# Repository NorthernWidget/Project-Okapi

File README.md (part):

# Okapi: Data logger with integrated solar charging and modular telemetry

***Okapi data logger (Resnik v0.4.0), with a micro-SD card for local storage and a Particle Boron telemetry module.***

The **Okapi** data logger responds to the need for a robust, flexible, and power-efficient open-source option to record and transmit data from remote locations. It is programmable using the open-source standard Arduino framework via a standard USB-C cable and supports a wide range of sensor input/output options. It connects to dual power supplies to ensure consistent recordings, and interfaces with a range of “Feather”-form-factor boards for telemetry.

## Namesake

The Okapi, a relative of the giraffe, communicates over long distances using [infrasound](https://en.wikipedia.org/wiki/Infrasound). The telemetry capabilities of this data logger inspired this namesake.

## Technical specifications

### Electronic Hardware

* Microcontroller (computer) core
  * ATMega1284p
  * Arduino compatible
  * Programmable using C++
  * 8 MHz
* Real-time clock
  * DS3231M
  * Temperature-compensated crystal for high accuracy (±5 ppm)
* Sensor and general-purpose connections
  * Primary Rail (selectable 3.3V or 5V)
    * I2C (up to 128 sensors permitted; expansion ports provided by Project Heptapod)
    * SPI
    * 2x 16-bit analog
    * Analog voltage reference
    * 12-bit Digital-to-analog conversion
    * 2x General-purpose input/output
    * USART
    * 2x Vbus (selectable 3.3V or 5V)
    * 2x Ground
  * Secondary Rail (selectable 3.3V or 5V)
    * I2C (up to 128 sensors permitted; expansion ports provided by Project Heptapod)
    * 2x 16-bit analog
    * 2x General-purpose input/output
    * USART
    * 2x Vbus (selectable 3.3V or 5V)
    * 2x Ground
* Data storage and return
  * Local storage: micro SD card
  * Telemetry: support for Feather-profile boards, including Particle devices:
    * Mobile phone networks
    * WiFi
    * Bluetooth
    * [In development] Iridium satellite
* Power
  * Dual power supply
  * Primary Power
    * Built-in maximum-power-point-tracking solar-charge-control circuitry
    * Lithium-Ion battery
  * Backup Power
    * Alkaline AA batteries
  * Real-time clock
    * Coin cell
  * Power consumption
    * Primary power, sleeping: 80 μA
    * Backup power, sleeping: 4 μA
    * Active (typical: data logger without sensors): 10 mA
    * Transmitting (mobile networks, typical: Particle Boron):
      * 16 mA background
      * 40 mA burst
  * Power generation
  * Solar, low light: 100 mA
* User interface
  * “Log” button: instantaneous reading (for testing)
  * “Reset” button
  * 2x 3-color indicator LEDs for the logger, a 3-color LED for the B-series module, and eight single LEDs on a PCA9634 LED driver
  * Computer readout via a serial monitor, included in the Arduino software
* Open-source licensing via CC BY-SA 4.0

>> @bschulz1701: Any updates needed? I think that there is also a WDT (correct?)

### Electronic Software and Firmware

* Programmable using the Arduino IDE https://www.arduino.cc/en/main/software
* Custom bootloader and board definition for ATMega1284p available via https://github.com/NorthernWidget/Arduino_Boards
* Custom libraries from Northern Widget and the open-source community
  * Primary data-logger functions
  * Libraries available with each sensor, exposing a standard interface
* Open-source licensing via GNU GPL 3.0

### Pinout and board interfaces

***Okapi data logger (Resnik v0.4.0) with pins, connectors, and interactive items annotated.***

**Pins are colored following this convention:**
* Ground: black
* Power supply: red
* Universal Serial Asynchronous Receiver--Transmitter (USART or UART): blue
* General-purpose I/O pins: gray
* Analog inputs and associated reference voltage: green
* Digital communications buses (SPI and I2C): purple
* Analog adjustable voltage output: salmon

**The power and programming connectors at the "south" end of the board are as follows:**
* USB-C connector (J10), to the logger's USB-serial converter (FT231X)
  * May be programmed using any USB-C cable that is not charging-only (i.e. that can carry data)
  * Can be used with our [clock-setting program](https://github.com/NorthernWidget/SetTime_GUI) to set the time on the real-time clock.
  * Provides power to the data logger while it is connected; this power source is isolated from the batteries and solar panel, and therefore may be plugged in safely at any time.
* Micro-USB connector (USB2), wired to the USB port of the B-series SoM on the M.2 socket, for that module rather than the logger
* Solar panel, up to 16 V open-circuit. A wide range of panels can work with this: as built the charger starts at 7.2 V, and [Solar charger set points](#solar-charger-set-points) gives the resistors for other panels. The charger accepts up to 32 V, but the v0.7.0 board's input capacitor (C10) is rated 16 V; [#44](https://github.com/NorthernWidget/Project-Okapi/issues/44) brings the full range in v0.8.0.
* Li-Ion battery, 2.60--4.475 V. This works with standard 18650 Li-ion batteries. It can work well with just a single battery, but if more storage is required, multiple 18650 batteries may be connected in parallel; we have a circuit-board design to do this: https://github.com/NorthernWidget/LiIon-18650-Parallel. ***CAUTION***: most commercially available multiple-18650-battery holders connect them in series; this voltage is ***TOO HIGH*** for the data logger.
* Primary batteries. This is ideally a pack of 3 primary (i.e., not reusable) Alkaline (or better) AA batteries with a long shelf life. The Okapi data logger will switch to these if its rechargeable power supply shuts down. The internal electronics reduce the quiescent power consumption while under backup power (see the above list of [electronic hardware technical specifications](#electronic-hardware)) and inform the logger about which power supply is being used, allowing it to, for example, reduce or temporarily terminate data transmission.

>> @bschulz1701: Solar panel supply current / size?

**"RST" and "LOG" buttons:**
* Reset ("RST"): stop the program that is currently executing on the main logger and return it to its boot sequence.
* Log Now ("LOG"): take a reading immediately. This is useful for diagnoses and testing.

>> General note: we may want to have an LED flash whenever the logger takes a reading -- even for 1/10 of a second. With an option to disable this, of course. But it is often better to know while in the field that a system is working

**Other notes, clockwise from the top:**
* The socket holds a [Feather-form-factor board](https://learn.adafruit.com/adafruit-feather/feather-specification).
  * This standard, designed by [Adafruit](https://www.adafruit.com/), has been widely adopted, including by the IoT/telemetry module designer [Particle](https://www.particle.io/).
  * We often use a [Particle Boron mobile-phone telemetry unit](https://docs.particle.io/boron/).
* Mounting holes for [\#4 screws](https://www.mcmaster.com/91772A106/)
* CR1220 battery; can power the real-time clock for up to 7 years
* ISP header (also called an ICSP header): This 3x2 header is used with an in-system programmer (in-circuit system programmer) to upload the [bootloader](#installing-the-bootloader) to the data logger.
* A micro-SD card holds a copy of all data, whether or not any telemetry is used

>> @bschulz1701: check my clock 7-year figure

***Okapi data logger (Resnik v0.4.0) with key microchips, LEDs, and switches marked.*** *MCU: Microcontroller. RTC: Real-time clock. LED: Light-emitting diode. Bus: a subsystem for connections and data transfer.*

The Okapi data logger contains two buses (see above), each of which has an independent voltage. The primary bus is on the left and the secondary bus is on the right. These can be selected as 3.3V (switches slid towards the inside of the board) or 5V (switches towards the outside of the board).

>> @bschulz1701: How much power can each bus source/sink?

Two LEDs, status and auxiliary, flash messages to the user to provide information on proper operations vs. a variety of possible errors. These are useful for field diagnoses, and are further described in [the field guide section, below](#field-operators-guide).

>> Design note: move STAT label to left of LED so it can be better seen

The Li-ion override button, which can be pressed with the tip of a pen or other small object, ...

>> @bschulz1701: This somehow overrides the Li-Ion battery electronics to allow something to happen... but I am not remembering what!

## On-board Devices

### I2C

| **Device** | **Address** | **Reprogrammable address** | **Function** |
|---|---|---|---|
| MLX90393 | 0x0C | N | Magnetometer |
| PAC1934 | 0x10 | N (R51) | Power monitor on the V_LI, V_PRIME, V_BETA and V_SOLAR_IN rails |
| BMA456 | 0x18 | N | Accelerometer |
| [MCP23018](https://github.com/NorthernWidget-Skunkworks/MCP23018) | 0x20 | N | I/O Expander |
| VEML6030 | 0x48 | N | Ambient light |
| [ADS1115](https://github.com/adafruit/Adafruit_ADS1X15) | 0x49 | N | ADC (sensor port), on the 5 V bus segment |
| MB85RC512T | 0x50 | N | FRAM |
| PCA9634 | 0x52 (also 0x03 and 0x70) | N | LED driver |
| MCP4726A2 | 0x62 | N | DAC, on the 5 V bus segment |
| [DS3231M](https://github.com/NorthernWidget/DS3231_Logger) | 0x68 | N | Real-time clock |
| [BME280](https://github.com/NorthernWidget/BME_Library) | 0x77 | N | On-board barometric pressure, temperature, and relative humidity |

### SPI

* SD Card

### UART (USART)

* FTDI USB-Serial converter
* Feather form-factor telemetry board; typically [Particle Boron](https://docs.particle.io/boron/)

## Assembly

Assembling this data logger is possible by hand with sufficient skill and the following tools:
* Temperature-controlled soldering iron
* Hot-air rework station
* Equipment for stenciling with solder paste
* ESD-safe tweezers and workstation
* Solder wick

Mechanized assembly by a professional circuit-board assembly house, which is available in many parts of the world, may be preferred due to the complexity of this data logger board.

**Do not build v0.7.0.** It is the 2024 design converted to KiCad, and the 2024 design's solar charger has no current-sense resistor: the LT3652's SENSE and BAT pins share one net, so it would charge the LiPo at its switch's current limit and never end the charge ([#32](https://github.com/NorthernWidget/Project-Okapi/issues/32)). v0.8.0 adds the resistor. The v0.7.0 files are the reference for that work.

The files for an assembly house are in `Production/`: the Gerbers, drill files and pick-and-place in `Okapi_0v7_2026-11-13.zip`, and the parts list in `Okapi_BoM_0v7_2026-11-13.csv`. `Production/make_production.sh` builds them from the KiCad design in `Hardware/KiCAD-10import/`. That project reads its symbols, footprints and title block from the Northern Widget KiCad library, [NW-Cold-Silicon](https://github.com/NorthernWidget/NW-Cold-Silicon), cloned into a folder beside this repository; the schematic and board carry their own copies of every symbol and footprint, so they open without it. The KiCad board is the 2024 Eagle board (`Hardware/Okapi.brd`) converted, and its copper, drills and placement match the 2024 fabrication files in `Hardware/Okapi_2024-11-02/` except where a recorded change differs (JP8 and R62 removed, smaller lands under R1, R5, R7, R8, C1 and C22, dual lands for R22, R48 and R69–R71, slots for the micro-USB shell, and the USB-C shell's slots and its link to ground).

>> THOUGHT: I have basic instructions for assembly on the [Project Walrus](https://github.com/NorthernWidget-Skunkworks/Project-TPDH-Walrus) README; I will not reproduce these here just yet, as we might want to set up a separate assembly guide, mostly with good links to existing resources, since our writing something of this nature would be to reinvent the wheel.

## Programming

### Downloading and installing the Arduino IDE

Go to https://www.arduino.cc/en/main/software. Choose the proper IDE version for your computer. For Windows, we suggest the non-app version to have more control over Arduino; this might change in the future. You will have to add custom libraries, so the web version will not work (at least, as of the time of writing). Download and install the Arduino IDE. Open it to begin the next steps.

### Installing the bootloader

Before a data logger can receive programs via the convenient USB port, it must have a *bootloader* that tells it to expect to receive new programs that way.  You can read more about bootloaders in general here: https://www.arduino.cc/en/Hacking/Bootloader.

Because you can't upload the bootloader via USB, you use the 2x3-pin 6-pin ICSP (also called ISP) header with a special device called an "in-circuit system programmer" (or just "in-system programmer; yup, that's what the acronym stands for).

Many devices exist to upload a bootloader including:
* The official [AVR ISP mkII](http://ww1.microchip.com/downloads/en/DeviceDoc/Atmel-42093-AVR-ISP-mkII_UserGuide.pdf) (no longer produced but available used)
* Using an [Arduino as an ISP](https://www.arduino.cc/en/tutorial/arduinoISP)
* The versatile [Olimex AVR-ISP-MK2](https://www.olimex.com/Products/AVR/Programmers/AVR-ISP-MK2/open-source-hardware)
* The [Adafruit USBtinyISP](https://www.adafruit.com/product/46)

To upload the bootloader, do the following:

1. Open the Arduino IDE. If you have not yet installed the Northern Widget board definitions, find and install them here (instructions provided): https://github.com/NorthernWidget/Arduino_Boards
2. Select the desired board -- most likely ***ATMega1284p 8MHz*** under *Northern Widget Boards*.
3. Plug the data logger into your computer via a USB-C cable to provide power.
4. Plug your ISP of choice into your computer (via a USB cable) and onto the 6-pin header. There are two ways to place it on; the header is aligned such that the ribbon cable should be facing away from the board while programming. If this fails without being able to upload, try flipping the header around.
5. Go to Tools --> Programmer and select the appropriate programmer based on what you are using.
6. Go to Tools --> Burn bootloader. Typically, within a few seconds, you learn whether you succeeded or failed. Hopefully it worked!

***Important note for Linux users:*** You must supply permissions to the Arduino IDE for it to be able to use the ICSP, or you will have to run it using `sudo`. The former option is better; the latter is easier in the moment.

***Note: Be sure to download and/or update drivers for your ISP.***

### Installing the requisite software libraries

>> @awickert: Add a full list of the requisite software to install; finish the firmware aggregator and use those directions (or the Arduino ones) to help users install that + sdfat. Include screenshots and host those directions at https://github.com/NorthernWidget-Skunkworks/Firmware-Aggregator.

### How to write a program

The below program is an example that you can copy and paste directly into the Arduino IDE in order to upload to your data logger. We'll walk you through what each piece of the code is and does.

#### Full program
```c++
/*
 * Okapi example: connected with a Walrus pressure--temperature sensor, often
 * used for water-level measurements, via the Longbow I2C/RS-485 translator.
 * Written by Bobby Schulz with a few comments added by Andy Wickert.
 */

#include "Okapi.h"
#include <TP_Downhole_Longbow.h>

TP_Downhole_Longbow Walrus; // Instantiate Walrus sensor; relict library name
Okapi Logger; // Instantiate data logger object

String Header = ""; // Information header; starts as an empty string
uint8_t I2CVals[1] = {0x22}; // I2C addresses of sensors

unsigned long UpdateRate = 60; // Number of seconds between readings

void setup() {
  Header = Header + Walrus.GetHeader();
  Logger.begin(I2CVals, sizeof(I2CVals), Header); // Pass header info to logger
  Init();
}

void loop() {
  Logger.run(Update, UpdateRate);
}

String Update()
{
  Init();
  delay(1500);
  return Walrus.GetString();
}

void Init()
{
  Walrus.begin(13, 0x22); // Instantiate Walrus (at address = 13)
                          // and Longbow Widget (at address = 0x22)
}
```

#### "Include" statements

```c++
#include "Okapi.h"
#include <TP_Downhole_Longbow.h>
```

These bring in the two code libraries involved, the former for the data logger and the latter for the sensors. This allows the user to access the classes and functions within these two libraries, as we will show in more detail below.

#### Instantiate a sensor object

```c++
TP_Downhole_Longbow Walrus; // Instantiate Walrus sensor; relict library name
Okapi Logger; // Instantiate data logger object
```

"Instantiating an object" means that we create our own specific versions of the a class of items. This can be thought of as: `Breakfast myBreakfast`. Breakfast is the general concept, but I create "myBreakfast", which I can then modify. In this same way, "Logger" is what we call our Okapi data logger, and "Walrus" is what we call our "TP_Downhole_Longbow" sensor; this name is a holdover from an earlier design that is the ancestor of the Walrus. We can then access functions and variables within these two instantiated objects.

#### Declare the header string

```c++
String Header = ""; // Information header; starts as an empty string
```

We start with an empty header, but will soon add information to it.

#### Create a list of the I2C addresses of the sensors

```c++
uint8_t I2CVals[1] = {0x22}; // I2C addresses of sensors
```

This is the trickiest step. You need to know what the I2C address of your sensor is. You can skip this, but then the logger will not run a check to see if the sensor is properly connected.

>> Let's make sure that we record this one each page, or find a way to replace this.

#### Declare the amount of time between logging events

```c++
unsigned long UpdateRate = 60; // Number of seconds between readings
```

This is the number of seconds between logging events. If it takes 2 seconds to record data, make sure that you give the logger at least 3 seconds between events. The maximum logging time is set by the watchdog timer, which [FINISH HERE]

>> @BSCHULZ1701: Is there an external WDT on Okapi?

#### `setup()` step: runs once at the start

```c++
void setup() {
  Header = Header + Walrus.GetHeader();
  Logger.begin(I2CVals, sizeof(I2CVals), Header); //Pass header info to logger
  Init();
}
```

`setup()` is a special function that runs just once when the logger boots up. In this case, it first adds the Walrus' header to the header string. `GetHeader()` is a standard function that lies within each of our sensor libraries and returns this header information as a `String`. We then pass the header and the I2C values to the Okapi library's `begin()` function. This sets up the header and prepares the data loger to record data. Finally, this function calls `Init()`, which we skip ahead to describe immediately below.

>> (awickert): I still don't understand why we have to pass `sizeof()` and can't just compute that within the function.

#### `Init()` function: skipping ahead to understand `setup()`

```c++
void Init()
{
  Walrus.begin(13, 0x22); // Instantiate Walrus (at address = 13)
                          // and Longbow Widget (at address = 0x22)
}
```

The `Init()` function calls the `begin()` function, standard within each Northern Widget sensor library, to instantiate the connection ports (e.g., I2C, RS-485) used to communicate between the sensor and the logger. In this case, there is only one sensor, but two ports are needed: An RS-485 signal goes from the Walrus to the Longbow Widget, which then converts the signal into an I2C signal with its own address. The reason for this is that an I2C signal can travel only ~3 m, but an RS-485 signal can travel ~100 m.

#### `loop()` step: keeps running until stopped

```c++
void loop() {
  Logger.run(Update, UpdateRate);
}
```

The loop calls the main function of the Okapi library, `run()`, repeatedly. This puts the logger into a low-power sleep mode and wakes it up only when interrupted by the clock or the "LOG" button. `Update` refers to the function described immediately below. `UpdateRate` is our logging interval defined above.

#### `Update()` function: Gives data for the logger to record

```c++
String Update()
{
  Init();
  delay(1500);
  return Walrus.GetString();
}
```

The `Update()` function first calls the `Init()` function to be sure that the sensor is ready to log. It then in this case delays 1500 milliseconds; this is an ad-hoc solution to the question of how long it takes the pressure transducer to settle after being started up, and is a safe large amount of time. This function then can `return` a string of all of the Walrus' readings (one pressure and two temperature measurements) separated by commas. This is then concatenated to a list of logger-internal measurements -- date/time; on-board temperature, pressure, and relative humidity; and onboard voltages for battery and solar-panel status -- and recorded to the SD card. If telemetry were present, these data could also be sent to a remote location.

### Reference

A full index of the public variables and functions within the Okapi data logger library is available at https://github.com/NorthernWidget/Okapi_Library.

>> Send user to library page

>> Thoughts: We should make all comments compatible with doxygen (following) what I did with the ALog library. It also looks like TravisCI has support for Arduino(!) This means that we could also automate construction of the documentation for these libraries.

### Integration with Particle Boron

>> @bschulz1701?

#### The 66-minute timer

The telemetry module (a Boron on the FeatherWing socket, or a B-SoM on the M.2 socket) is not powered all the time. Its battery input comes through a load switch (U10) that a TPL5111 timer (U8) controls, and the timer runs on its own clock with an interval set by R20: 130 kΩ gives 66 minutes (3943 s by the TPL5111 datasheet's Equation 1; 3854 to 4033 s with a 1 % resistor). The 2024 Eagle files also carry JP8, which selects R62 (330 kΩ) instead. That value is above the part's 170 kΩ maximum and does nothing, and the KiCad board removes both (#34).

Three things happen on that interval:

1. **It powers the module every 66 minutes whether or not the logger asks.** This is the purpose of the timer: a cellular module receives only while it is powered and attached, so the hourly wake is the window in which a command, a request to resend, or a firmware update for the module can arrive from outside, and the slowest the module can ever be heard from is once an interval, even if the ATmega is asleep past its schedule or hung. For that to work the module must connect on every wake, not only when it has rows to send, and then say it is done.
2. **It bounds every session.** From the moment the module is powered, by the timer or by the logger, it has at most one interval before the timer cuts its power for 50 ms and starts over. A module that hangs is power-cycled once an hour, and this is the only reset path to the module on the board.
3. **It is the counter the logger restarts.** Pulling PARTICLE_EN low for 20 to 30 ms (expander port B pin 7, through Q3 onto the timer's DELAY/M_DRV pin) powers the module at once and restarts the interval. Hold it low and the module stays on past the interval, so pulse it. A request while the module is already on is ignored.

The module ends its own session by pulsing WD_DONE (the FeatherWing's A3, the B-SoM's ADC3): the timer drops the switch and the module draws nothing until the next interval or the next request. The 2019 Boron sketch does this from a 90-second watchdog that it refreshes on every line received from the logger, so the module stays up while rows arrive and shuts itself off 90 seconds after the last one.

As of 2026-11-05 the logger firmware does not drive PARTICLE_EN (Okapi_Library's backhaul writes the pin high, which on the open-drain expander releases it, and never configures it as an output), so on the boards in the field the timer alone powers the module and the backhaul succeeds only when it lands inside a module's on-window. The intended cycle, pulse PARTICLE_EN when there are rows to send and let the module pulse DONE when they are sent, is the firmware fix on the list.

## Wiring

>> Example needed

## Power supply

* **Lithium-ion 18650 rechargeable batteries**; this board can hold two in parallel: https://github.com/NorthernWidget/LiIon-18650-Parallel
* **Solar panel**. A wide range is acceptable, but we like [Voltaic Systems' 6-watt panel](https://voltaicsystems.com/6-watt-panel/). If you do not want to snip off the barrel jack, [this extension plug from Adafruit should work](https://www.adafruit.com/product/2788) (though we have not tested it... and you'll also have to cut *it* in half).
* **Primary alkaline batteries**; we typically use three high-quality (e.g., Duracell) AAs. These are the backup power supply, and we place them in a [3xAA holder (in series for the proper voltage) with a switch](https://www.jameco.com/z/SBH-331-AS-R-3x-AA-Battery-Holder-with-Cover-and-Switch_216144.html).

>> @bschulz1701: new smarter 18650 holder?

### Solar charger set points

Two resistor pairs set how the LT3652 charger (U4) uses your panel. Both sit on lands that take an 0402 or an 0603 part, so you can change them by hand to suit the panel you deploy:

* **MPPT, R22 over R69.** The charger holds the panel at 2.7 V × (1 + R22 / R69), close to the panel's maximum-power voltage, and draws less current rather than let the panel sag below it.
* **Start, R71 over R70.** The charger starts once the panel rises above 1.2 V × (1 + R71 / R70). Keep this below the panel's open-circuit voltage. The charger also needs the panel about 3.3 V above the cell to start (7.5 V on a full cell).

| Panel | Examples | R22 / R69 | MPPT | R71 / R70 | Start | Board |
|---|---|---|---|---|---|---|
| 6 V, 12-cell (as built) | Voltaic P126 (2 W); older 6 V panels such as Voltaic's 6 W P106C | 143 kΩ / 100 kΩ | 6.56 V | 1 MΩ / 200 kΩ | 7.2 V | v0.7.0 |
| 5–6 V, 10-cell ETFE | Voltaic P105, P110, P120, P124 | 143 kΩ / 120 kΩ | 5.92 V | 1 MΩ / 205 kΩ | 7.05 V | v0.7.0 |
| 12 V, 36-cell | Campbell SP10 and SP20, Renogy RNG-10D-SS, Ameresco 10M and 20J, Voltaic P108 and P152 | 1 MΩ / 200 kΩ | 16.2 V | 1 MΩ / 100 kΩ | 13.2 V | v0.8.0 |

As built, a 10-cell panel cannot always start the charger: its open-circuit voltage (6.6–7.3 V at 25 °C) sits at or below the 7.2 V start threshold, and lower still on a warm day. Change R70 to 205 kΩ, and R69 to 120 kΩ for the lower maximum-power voltage. A 12 V panel reaches 27 V open-circuit at −40 °C, beyond the 16 V input capacitor on v0.7.0, so 12 V panels wait for v0.8.0 ([#44](https://github.com/NorthernWidget/Project-Okapi/issues/44), [#46](https://github.com/NorthernWidget/Project-Okapi/issues/46)). Panel figures are from the makers' datasheets; the study behind this table is in NW-Status (`studies/okapi-hardware-audit/sources/2026-11-09-solar-panels-agent-report.md`).

### Regulator feedback dividers

The two adjustable regulators set their outputs with resistor dividers that follow their datasheets: the TLV61220 (U1, the 5 V core boost) with R4 1.62 MΩ over R5 180 kΩ, the datasheet's own example value for the lower resistor, and the TPS62822 (U2, the 3.3 V aux buck) with R6 820 kΩ over R7 180 kΩ and C6 68 pF as its feed-forward capacitor, which is the datasheet's 12 ms / R2 exactly.

The TPS62822's divider sits above the datasheet's center value (R2 of 100 kΩ, at most 120 kΩ, for 5 µA in the divider). That is a trade the datasheet names: a lower divider buys noise immunity at the FB node and costs light-load efficiency. Here the divider draws 3.3 µA instead of 6 µA, about 9 µW less from a rail that spends its life at light load and is switched off in sleep, and the node's sensitivity to pin bias and leakage is about twice the datasheet's, which on a regulator with a 1 % reference feeding sensors through their own switches is below anything measurable. Decided 2026-11-05 to keep the values as built (Project-Okapi #22).

### Sensor port current limits

Each sensor bus (PRIME and SEC) is fed through a pair of MIC2544 high-side switches, one from the 5 V rail and one from the 3.3 V rail. A slide switch on each bus (S1 for SEC, S2 for PRIME) picks 5 V or 3.3 V, and the firmware turns the bus on or off. Logic gates make the two choices exclusive: an AND gate passes the bus enable to the 5 V switch only when the slide is at 5 V, and through an inverter to the 3.3 V switch only when it is not, so both can never be on together. On v0.7.0, move a slide switch only with the logger off: between positions its common pin floats, and the gates may then turn both switches on together. v0.8.0 adds a pull-down that holds the 3.3 V side while the slider moves ([#53](https://github.com/NorthernWidget/Project-Okapi/issues/53)), so you can move it with the logger running. Set it to your sensor's voltage before you connect the sensor. Each switch limits its output current with a resistor on its ILIM pin: 232 Ω for 1 A, which is the default on every port.

To let one port draw up to 1.5 A, close its solder jumper (JP1 to JP4, one per switch). This puts 464 Ω in parallel with the 232 Ω, 154.7 Ω in all, which is the most the MIC2544 is rated to pass: its ILIM resistor may be no smaller than 154 Ω.

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
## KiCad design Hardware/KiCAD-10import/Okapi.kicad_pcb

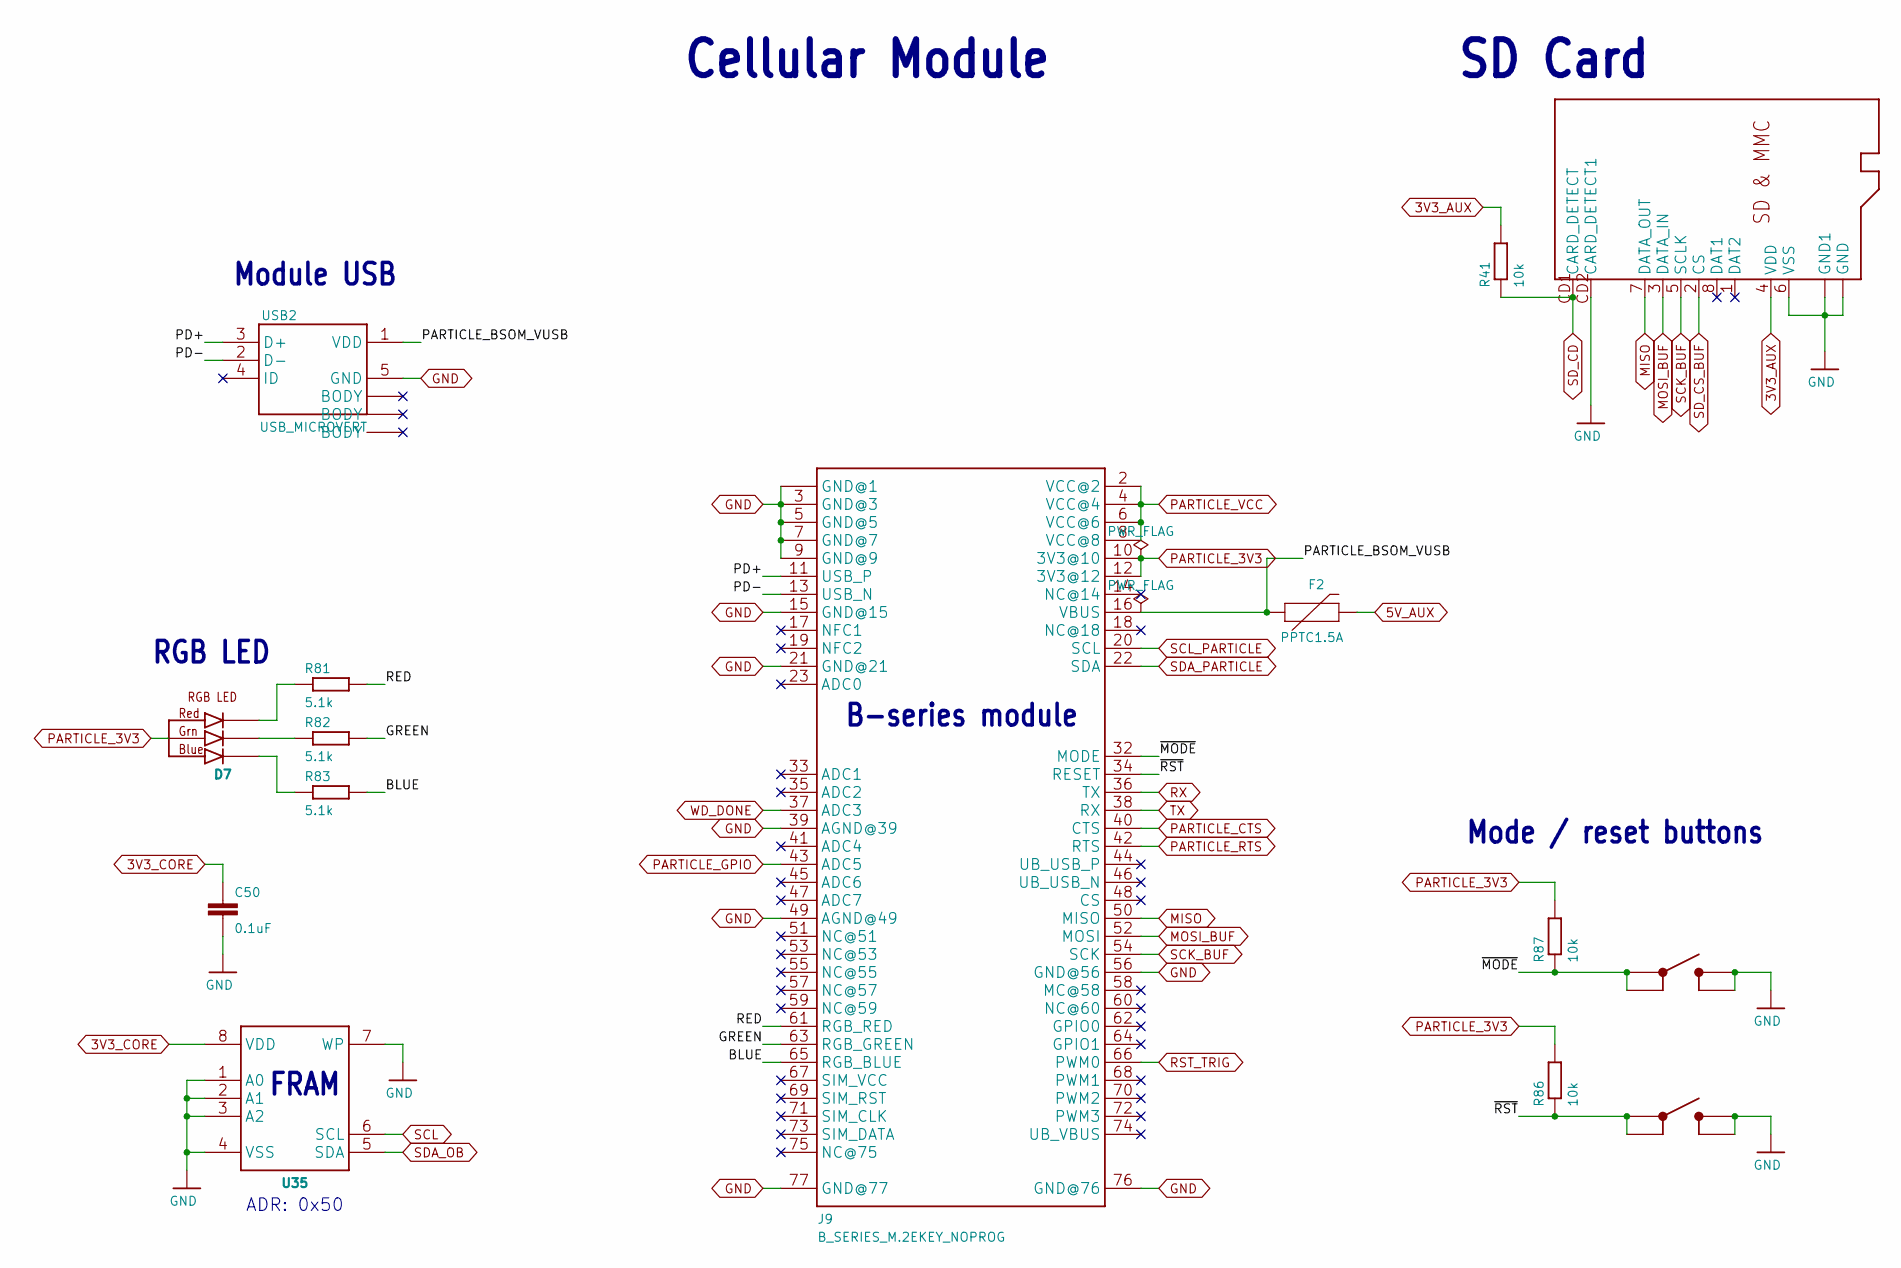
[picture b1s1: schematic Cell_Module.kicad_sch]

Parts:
C50: 0.1uF; C0402; MPN GCM155R71C104KA55D; DIGIKEY 490-4759-1-ND
D7: CLVBA-FKA; MPN CLVBA-FKA-CAEDH8BBB7A363; DIGIKEY CLVBA-FKA-CAEDH8BBB7A363CT-ND
F2: PPTC1.5A; 1206; MPN MF-NSMF150-2; DIGIKEY MF-NSMF150-2CT-ND
J9: B_SERIES_M.2EKEY_NOPROG; PARTICLE_M.2EKEY_NOPROG; MPN 2199230-4; DIGIKEY A115904CT-ND
R41, R86, R87: 10k; R0402; MPN RC0402FR-0710KL; DIGIKEY 311-10.0KLRCT-ND
R81, R82, R83: 5.1k; R0402; MPN RC0402FR-075K1L; DIGIKEY 311-5.10KLRCT-ND
S6, S7: BUTTON4.2X3.2; SWITCH_4.2X3.2; MPN PTS810 SJG 250 SMTR LFS; DIGIKEY CKN10504CT-ND
SD1: MICROSDCD; MICROSD_CD; MPN 5025700893; DIGIKEY WM19093CT-ND
U35: MB85RC; SO08; MPN MB85RC512TPNF-G-JNERE1; DIGIKEY 865-1269-1-ND
USB2: USB_MICROVERT; USB_MICRO_VERT_MOLEX; MPN 1051330001; DIGIKEY WM9734CT-ND

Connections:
3V3_AUX: R41.2, SD1.4 (VDD); also elsewhere on the board
3V3_CORE: C50.1, U35.8 (VDD); also elsewhere on the board
5V_AUX: F2.2; also elsewhere on the board
/Cell_Module/BLUE: J9.65 (RGB_BLUE), R83.2
/Cell_Module/GREEN: J9.63 (RGB_GREEN), R82.2
/Cell_Module/PARTICLE_BSOM_VUSB: F2.1, J9.16 (VBUS), USB2.1 (VDD)
/Cell_Module/PD+: J9.11 (USB_P), USB2.3 (D+)
/Cell_Module/PD-: J9.13 (USB_N), USB2.2 (D-)
/Cell_Module/RED: J9.61 (RGB_RED), R81.2
/Cell_Module/~MODE: J9.32 (MODE), R87.1, S6.1, S6.2
/Cell_Module/~RST: J9.34 (RESET), R86.1, S7.1, S7.2
GND: C50.2, J9.1 (GND@1), J9.3 (GND@3), J9.5 (GND@5), J9.7 (GND@7), J9.9 (GND@9), J9.15 (GND@15), J9.21 (GND@21), J9.39 (AGND@39), J9.49 (AGND@49), J9.56 (GND@56), J9.76 (GND@76), J9.77 (GND@77), J9.GND (GND@1), S6.3 (4), S6.4 (3), S7.3 (4), S7.4 (3), SD1.6 (VSS), SD1.CD2 (CARD_DETECT1), SD1.MT1 (GND), SD1.MT2 (GND1), SD1.MT3 (GND1), SD1.MT4 (GND1), U35.1 (A0), U35.2 (A1), U35.3 (A2), U35.4 (VSS), U35.7 (WP), USB2.5 (GND); also elsewhere on the board
MISO: J9.50 (MISO), SD1.7 (DATA_OUT); also elsewhere on the board
MOSI_BUF: J9.52 (MOSI), SD1.3 (DATA_IN); also elsewhere on the board
unnamed: D7.3 (BLUE_CATH), R83.1
unnamed: D7.4 (GREEN_CATH), R82.1
unnamed: D7.1 (RED_CATH), R81.1
PARTICLE_3V3: D7.2 (ANODE), J9.10 (3V3@10), J9.12 (3V3@12), R86.2, R87.2; also elsewhere on the board
PARTICLE_CTS: J9.40 (CTS); also elsewhere on the board
PARTICLE_GPIO: J9.43 (ADC5); also elsewhere on the board
PARTICLE_RTS: J9.42 (RTS); also elsewhere on the board
PARTICLE_VCC: J9.2 (VCC@2), J9.4 (VCC@4), J9.6 (VCC@6), J9.8 (VCC@8); also elsewhere on the board
RST_TRIG: J9.66 (PWM0); also elsewhere on the board
RX: J9.36 (TX); also elsewhere on the board
SCK_BUF: J9.54 (SCK), SD1.5 (SCLK); also elsewhere on the board
SCL: U35.6 (SCL); also elsewhere on the board
SCL_PARTICLE: J9.20 (SCL); also elsewhere on the board
SDA_OB: U35.5 (SDA); also elsewhere on the board
SDA_PARTICLE: J9.22 (SDA); also elsewhere on the board
SD_CD: R41.1, SD1.CD1 (CARD_DETECT); also elsewhere on the board
SD_CS_BUF: SD1.2 (CS); also elsewhere on the board
TX: J9.38 (RX); also elsewhere on the board
WD_DONE: J9.37 (ADC3); also elsewhere on the board

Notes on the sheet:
Cellular Module
B-series module
RGB LED
Mode / reset buttons
ADR: 0x50
Module USB
FRAM
SD Card

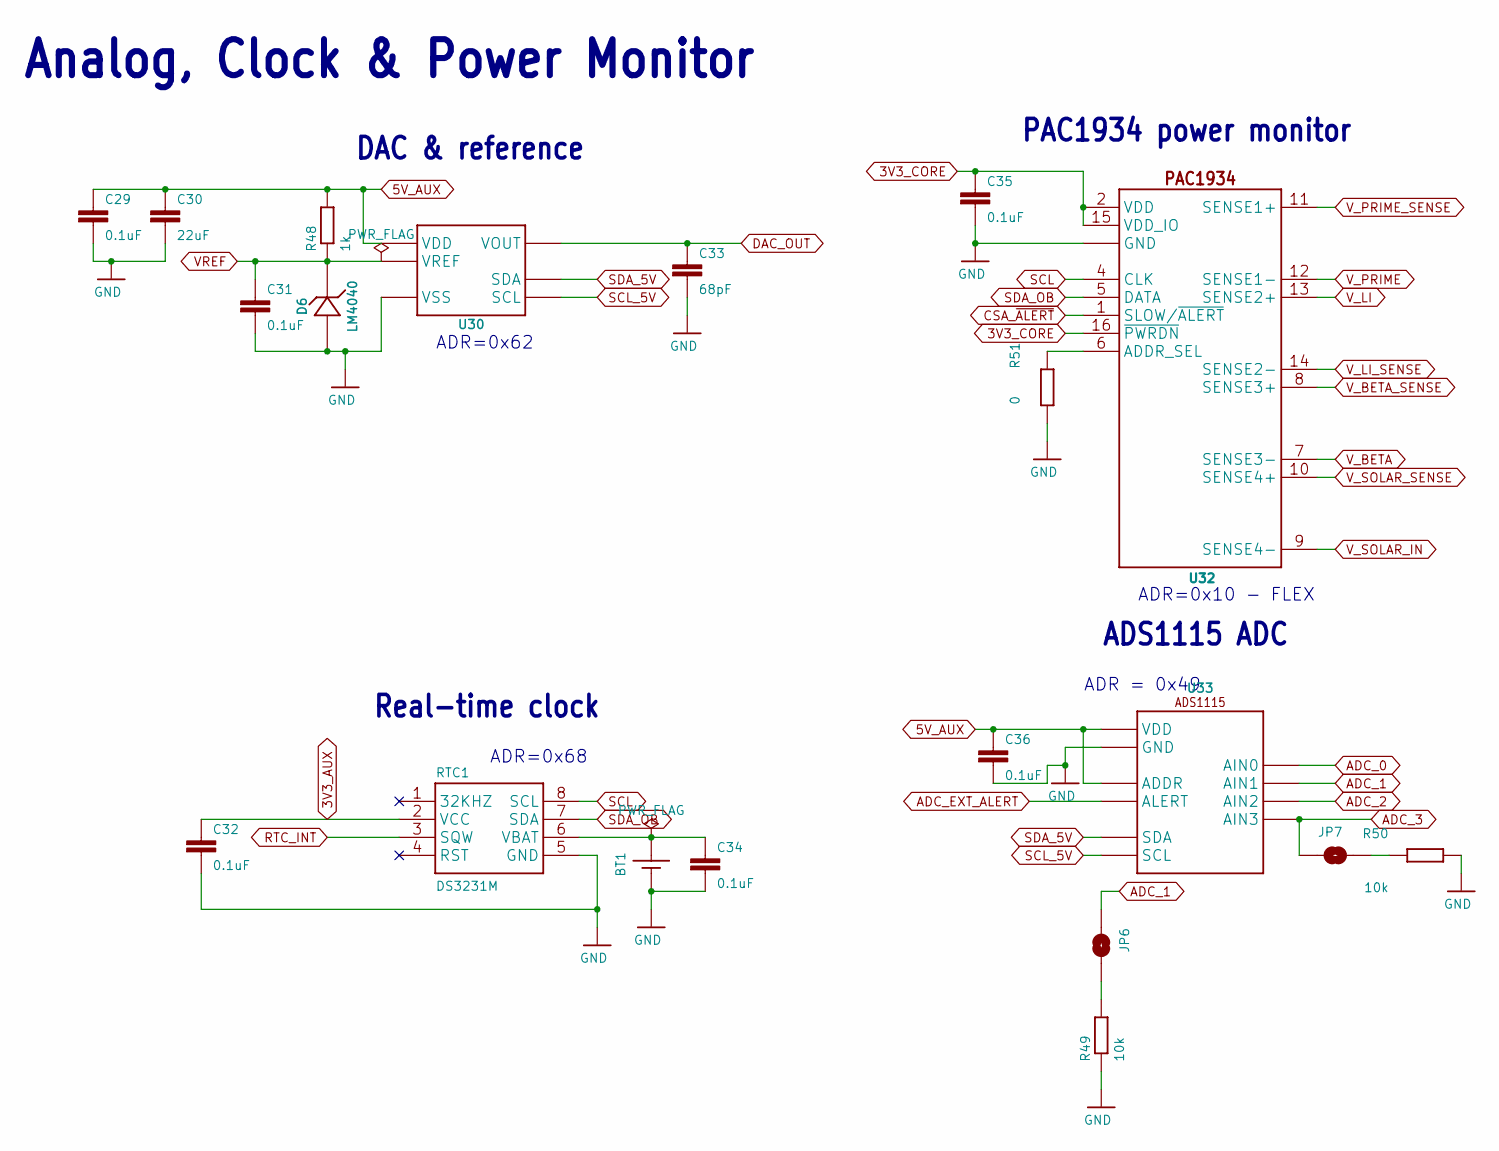
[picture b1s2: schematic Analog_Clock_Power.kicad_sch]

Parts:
BT1: BATTERY_COIN12MM; LINX_BAT-HLD-012-SMT; MPN BK-916-TR; DIGIKEY BK-916-CT-ND
C29, C31, C32, C34, C35, C36: 0.1uF; C0402; MPN GCM155R71C104KA55D; DIGIKEY 490-4759-1-ND
C30: 22uF; C0805; MPN GRM219R61C226ME15L; DIGIKEY 490-9952-1-ND
C33: 68pF; C0402; MPN 885012005060; DIGIKEY 732-7474-1-ND
D6: LM4040; SOT23-3; MPN LM4040DYM3-2.5-TR; DIGIKEY 576-1047-1-ND
JP6, JP7: JUMPER-SMT_2_NO_SILK; SMT-JUMPER_2_NO_SILK
R48: 1k; R0402_0603; MPN RC0402FR-071KL; DIGIKEY 311-1.00KLRCT-ND
R49, R50: 10k; R0603; MPN CRT0603-BY-1002ELF; DIGIKEY CRT0603-BY-1002ELFCT-ND
R51: 0; R0402; MPN ERJ-2GE0R00X; DIGIKEY P0.0JCT-ND
RTC1: DS3231M; SO08; MPN DS3231MZ+; DIGIKEY DS3231MZ+-ND
U30: MCP4726SOT-23; SOT23-6L; MPN MCP4726A2T-E/CH; DIGIKEY MCP4726A2T-E/CHCT-ND
U32: PAC1934QFN; QFN16; MPN PAC1934T-I/JQ; DIGIKEY PAC1934T-I/JQCT-ND
U33: ADS111; VSSOP_10; MPN ADS1115IDGSR; DIGIKEY 296-38849-1-ND

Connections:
3V3_AUX: C32.1, RTC1.2 (VCC); also elsewhere on the board
3V3_CORE: C35.1, U32.2 (VDD), U32.15 (VDD_IO), U32.16 (~PWRDN); also elsewhere on the board
5V_AUX: C29.1, C30.1, C36.1, R48.2, U30.3 (VDD), U33.1 (ADDR), U33.8 (VDD); also elsewhere on the board
ADC_0: U33.4 (AIN0); also elsewhere on the board
ADC_1: JP6.1, U33.5 (AIN1); also elsewhere on the board
ADC_2: U33.6 (AIN2); also elsewhere on the board
ADC_3: JP7.1, U33.7 (AIN3); also elsewhere on the board
ADC_EXT_ALERT: U33.2 (ALERT); also elsewhere on the board
CSA_~ALERT: U32.1 (SLOW/~ALERT); also elsewhere on the board
DAC_OUT: C33.1, U30.1 (VOUT); also elsewhere on the board
GND: BT1.GND (-), C29.2, C30.2, C31.2, C32.2, C33.2, C34.2, C35.2, C36.2, D6.2 (A), R49.1, R50.1, R51.1, RTC1.5 (GND), U30.2 (VSS), U32.3 (GND), U32.EP (GND), U33.3 (GND); also elsewhere on the board
unnamed: BT1.POWER0 (+), C34.1, RTC1.6 (VBAT)
unnamed: JP6.2, R49.2
unnamed: JP7.2, R50.2
unnamed: R51.2, U32.6 (ADDR_SEL)
RTC_INT: RTC1.3 (SQW); also elsewhere on the board
SCL: RTC1.8 (SCL), U32.4 (CLK); also elsewhere on the board
SCL_5V: U30.5 (SCL), U33.10 (SCL); also elsewhere on the board
SDA_5V: U30.4 (SDA), U33.9 (SDA); also elsewhere on the board
SDA_OB: RTC1.7 (SDA), U32.5 (DATA); also elsewhere on the board
VREF: C31.1, D6.1 (C), R48.1, U30.6 (VREF); also elsewhere on the board
V_BETA: U32.7 (SENSE3-); also elsewhere on the board
V_BETA_SENSE: U32.8 (SENSE3+); also elsewhere on the board
V_LI: U32.13 (SENSE2+); also elsewhere on the board
V_LI_SENSE: U32.14 (SENSE2-); also elsewhere on the board
V_PRIME: U32.12 (SENSE1-); also elsewhere on the board
V_PRIME_SENSE: U32.11 (SENSE1+); also elsewhere on the board
V_SOLAR_IN: U32.9 (SENSE4-); also elsewhere on the board
V_SOLAR_SENSE: U32.10 (SENSE4+); also elsewhere on the board

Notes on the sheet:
ADR=0x68
ADR = 0x49
Analog, Clock & Power Monitor
Real-time clock
ADR=0x10 - FLEX
DAC & reference
ADS1115 ADC
ADR=0x62
PAC1934 power monitor

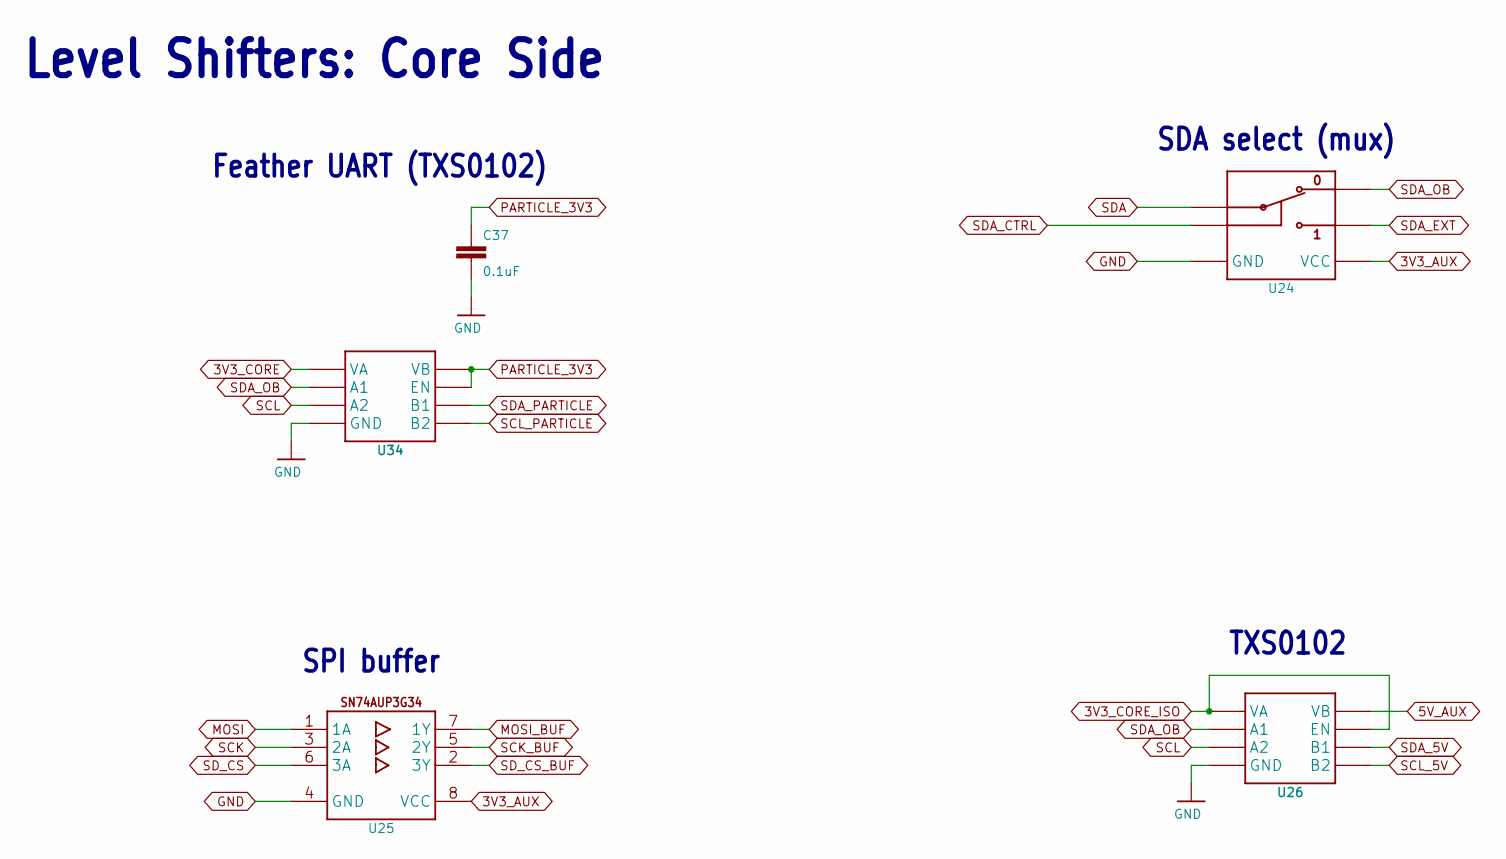
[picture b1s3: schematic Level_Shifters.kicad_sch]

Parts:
C37: 0.1uF; C0402; MPN GCM155R71C104KA55D; DIGIKEY 490-4759-1-ND
U24: SN74LVC1G3157DRL; DRL_R-PDSO-N6; MPN SN74LVC1G3157DRLR; DIGIKEY 296-18015-1-ND
U25: SN74AUP3G34DCU; DCU_(R-PDSO-G8); MPN SN74AUP3G34DCUR; DIGIKEY 296-25595-1-ND
U26, U34: TXS0102DQM; DQM_R-PX2SON-N8; MPN TXS0102DQMR; DIGIKEY 296-28435-1-ND

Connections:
3V3_AUX: U24.5 (VCC), U25.8 (VCC); also elsewhere on the board
3V3_CORE: U34.1 (VA); also elsewhere on the board
3V3_CORE_ISO: U26.1 (VA), U26.5 (EN); also elsewhere on the board
5V_AUX: U26.8 (VB); also elsewhere on the board
GND: C37.2, U24.2 (GND), U25.4 (GND), U26.4 (GND), U34.4 (GND); also elsewhere on the board
MOSI: U25.1 (1A); also elsewhere on the board
MOSI_BUF: U25.7 (1Y); also elsewhere on the board
PARTICLE_3V3: C37.1, U34.5 (EN), U34.8 (VB); also elsewhere on the board
SCK: U25.3 (2A); also elsewhere on the board
SCK_BUF: U25.5 (2Y); also elsewhere on the board
SCL: U26.3 (A2), U34.3 (A2); also elsewhere on the board
SCL_5V: U26.6 (B2); also elsewhere on the board
SCL_PARTICLE: U34.6 (B2); also elsewhere on the board
SDA: U24.4 (A); also elsewhere on the board
SDA_5V: U26.7 (B1); also elsewhere on the board
SDA_CTRL: U24.6 (S); also elsewhere on the board
SDA_EXT: U24.1 (B2); also elsewhere on the board
SDA_OB: U24.3 (B1), U26.2 (A1), U34.2 (A1); also elsewhere on the board
SDA_PARTICLE: U34.7 (B1); also elsewhere on the board
SD_CS: U25.6 (3A); also elsewhere on the board
SD_CS_BUF: U25.2 (3Y); also elsewhere on the board

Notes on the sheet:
TXS0102
Feather UART (TXS0102)
Level Shifters: Core Side
SDA select (mux)
SPI buffer

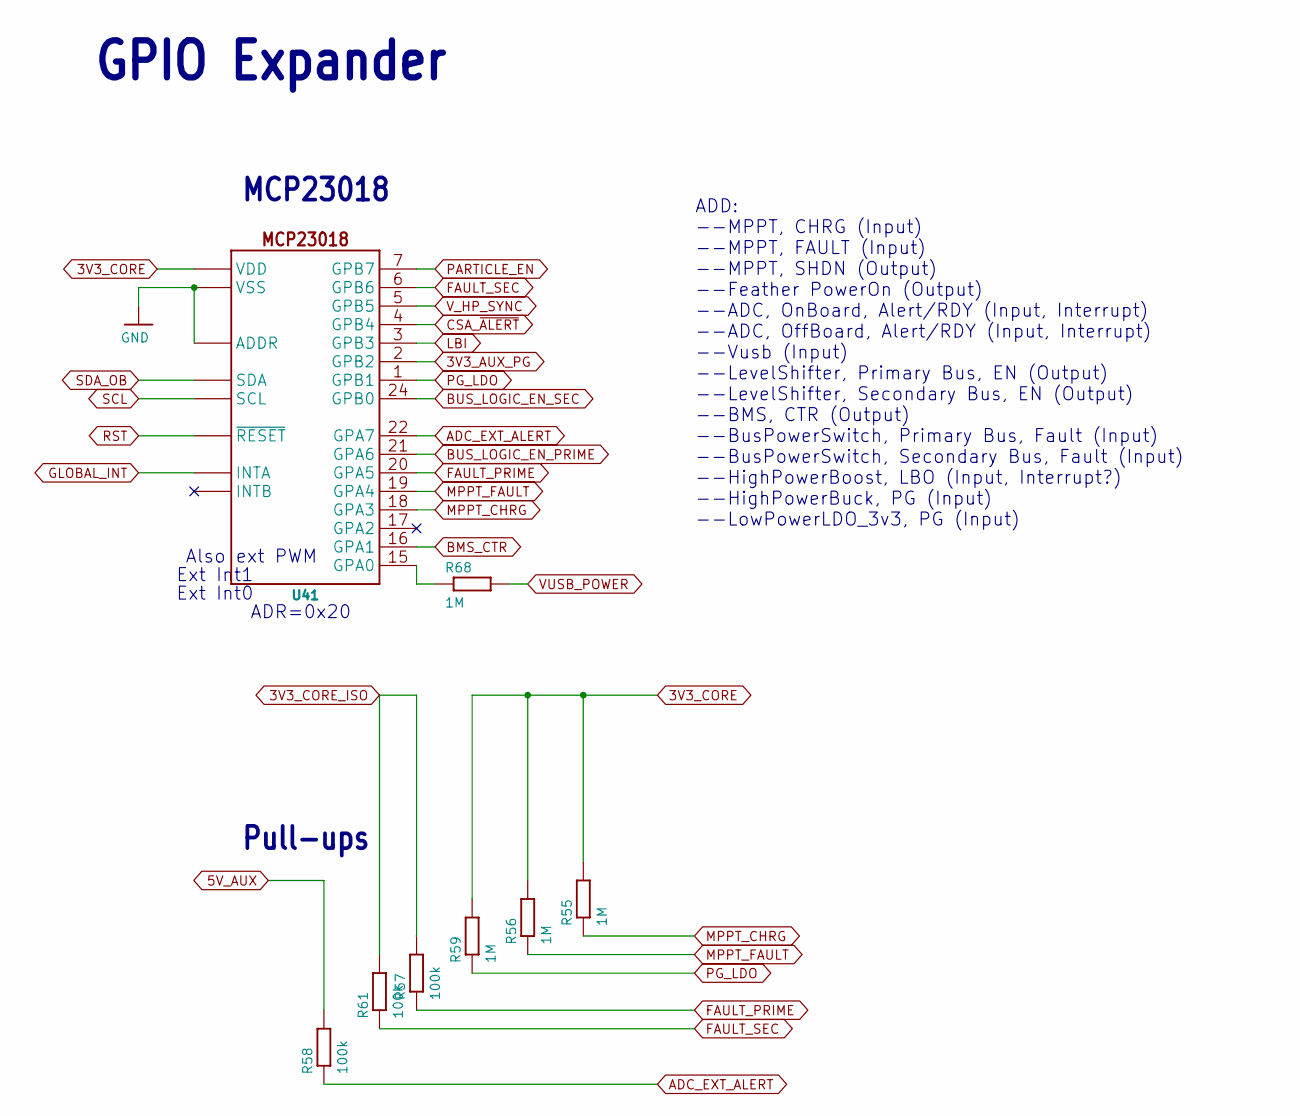
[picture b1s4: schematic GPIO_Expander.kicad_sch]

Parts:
R55, R56, R59, R68: 1M; R0402; MPN RC0402FR-071ML; DIGIKEY 311-1.00MLRCT-ND
R57, R58, R61: 100k; R0402; MPN RC0402FR-07100KL; DIGIKEY 311-100KLRCT-ND
U41: MCP23018QFN; QFN24; MPN MCP23018T-E/MJ; DIGIKEY MCP23018T-E/MJCT-ND

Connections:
3V3_AUX_PG: U41.2 (GPB2); also elsewhere on the board
3V3_CORE: R55.2, R56.2, R59.2, U41.8 (VDD); also elsewhere on the board
3V3_CORE_ISO: R57.2, R61.2; also elsewhere on the board
5V_AUX: R58.2; also elsewhere on the board
ADC_EXT_ALERT: R58.1, U41.22 (GPA7); also elsewhere on the board
BMS_CTR: U41.16 (GPA1); also elsewhere on the board
BUS_LOGIC_EN_PRIME: U41.21 (GPA6); also elsewhere on the board
BUS_LOGIC_EN_SEC: U41.24 (GPB0); also elsewhere on the board
CSA_~ALERT: U41.4 (GPB4); also elsewhere on the board
FAULT_PRIME: R57.1, U41.20 (GPA5); also elsewhere on the board
FAULT_SEC: R61.1, U41.6 (GPB6); also elsewhere on the board
GLOBAL_INT: U41.14 (INTA); also elsewhere on the board
GND: U41.11 (ADDR), U41.23 (VSS), U41.EP (VSS); also elsewhere on the board
LBI: U41.3 (GPB3); also elsewhere on the board
MPPT_CHRG: R55.1, U41.18 (GPA3); also elsewhere on the board
MPPT_FAULT: R56.1, U41.19 (GPA4); also elsewhere on the board
unnamed: R68.1, U41.15 (GPA0)
PARTICLE_EN: U41.7 (GPB7); also elsewhere on the board
PG_LDO: R59.1, U41.1 (GPB1); also elsewhere on the board
RST: U41.12 (~RESET); also elsewhere on the board
SCL: U41.9 (SCL); also elsewhere on the board
SDA_OB: U41.10 (SDA); also elsewhere on the board
VUSB_POWER: R68.2; also elsewhere on the board
V_HP_SYNC: U41.5 (GPB5); also elsewhere on the board

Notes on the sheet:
Ext Int0
Ext Int1
Also ext PWM
Pull-ups
MCP23018
GPIO Expander
ADR=0x20
ADD: --MPPT, CHRG (Input) --MPPT, FAULT (Input) --MPPT, SHDN (Output) --Feather PowerOn (Output) --ADC, OnBoard, Alert/RDY (Input, Interrupt) --ADC, OffBoard, Alert/RDY (Input, Interrupt) --Vusb (Input) --LevelShifter, Primary Bus, EN (Output) --LevelShifter, Secondary Bus, EN (Output) --BMS, CTR (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

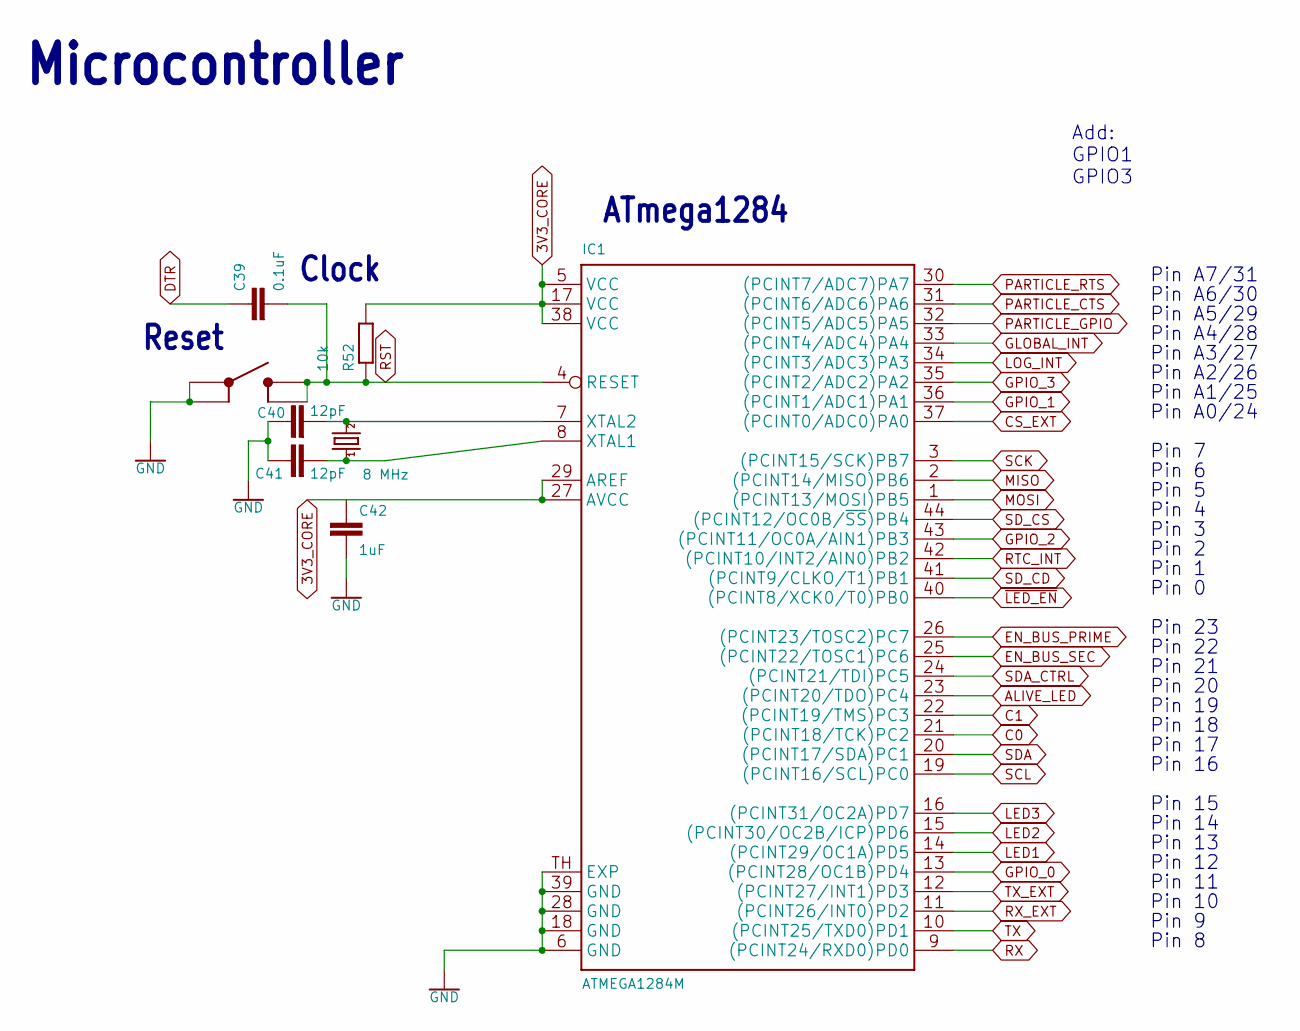
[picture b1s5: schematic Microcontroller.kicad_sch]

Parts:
C39: 0.1uF; C0402; MPN GCM155R71C104KA55D; DIGIKEY 490-4759-1-ND
C40, C41: 12pF; C0402; MPN CGA2B2C0G1H120J050BA; DIGIKEY 445-5585-1-ND
C42: 1uF; C0402; MPN CL05A105KA5NQNC; DIGIKEY 1276-1445-1-ND
IC1: ATMEGA1284M; MLF44-TH; MPN ATMEGA1284P-MUR; DIGIKEY ATMEGA1284P-MURCT-ND
R52: 10k; R0402; MPN RC0402FR-0710KL; DIGIKEY 311-10.0KLRCT-ND
S4: BUTTON4.2X3.2; SWITCH_4.2X3.2; MPN PTS810 SJG 250 SMTR LFS; DIGIKEY CKN10504CT-ND
XTAL1: 8 MHz; CRYSTAL_5X3.2_2-SMD; MPN ECS-80-12-30-JGN-TR; DIGIKEY 50-ECS-80-12-30-JGN-CT-ND

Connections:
3V3_CORE: C42.1, IC1.5 (VCC), IC1.17 (VCC), IC1.27 (AVCC), IC1.29 (AREF), IC1.38 (VCC), R52.2; also elsewhere on the board
ALIVE_LED: IC1.23 ((PCINT20/TDO)PC4); also elsewhere on the board
C0: IC1.21 ((PCINT18/TCK)PC2); also elsewhere on the board
C1: IC1.22 ((PCINT19/TMS)PC3); also elsewhere on the board
CS_EXT: IC1.37 ((PCINT0/ADC0)PA0); also elsewhere on the board
DTR: C39.1; also elsewhere on the board
EN_BUS_PRIME: IC1.26 ((PCINT23/TOSC2)PC7); also elsewhere on the board
EN_BUS_SEC: IC1.25 ((PCINT22/TOSC1)PC6); also elsewhere on the board
GLOBAL_INT: IC1.33 ((PCINT4/ADC4)PA4); also elsewhere on the board
GND: C40.1, C41.1, C42.2, IC1.6 (GND), IC1.18 (GND), IC1.28 (GND), IC1.39 (GND), IC1.TH (EXP), S4.1, S4.2; also elsewhere on the board
GPIO_0: IC1.13 ((PCINT28/OC1B)PD4); also elsewhere on the board
GPIO_1: IC1.36 ((PCINT1/ADC1)PA1); also elsewhere on the board
GPIO_2: IC1.43 ((PCINT11/OC0A/AIN1)PB3); also elsewhere on the board
GPIO_3: IC1.35 ((PCINT2/ADC2)PA2); also elsewhere on the board
LED1: IC1.14 ((PCINT29/OC1A)PD5); also elsewhere on the board
LED2: IC1.15 ((PCINT30/OC2B/ICP)PD6); also elsewhere on the board
LED3: IC1.16 ((PCINT31/OC2A)PD7); also elsewhere on the board
LOG_INT: IC1.34 ((PCINT3/ADC3)PA3); also elsewhere on the board
MISO: IC1.2 ((PCINT14/MISO)PB6); also elsewhere on the board
MOSI: IC1.1 ((PCINT13/MOSI)PB5); also elsewhere on the board
unnamed: C41.2, IC1.8 (XTAL1), XTAL1.OSC1 (1)
unnamed: C40.2, IC1.7 (XTAL2), XTAL1.OSC2 (2)
PARTICLE_CTS: IC1.31 ((PCINT6/ADC6)PA6); also elsewhere on the board
PARTICLE_GPIO: IC1.32 ((PCINT5/ADC5)PA5); also elsewhere on the board
PARTICLE_RTS: IC1.30 ((PCINT7/ADC7)PA7); also elsewhere on the board
RST: C39.2, IC1.4 (RESET), R52.1, S4.3 (4), S4.4 (3); also elsewhere on the board
RTC_INT: IC1.42 ((PCINT10/INT2/AIN0)PB2); also elsewhere on the board
RX: IC1.9 ((PCINT24/RXD0)PD0); also elsewhere on the board
RX_EXT: IC1.11 ((PCINT26/INT0)PD2); also elsewhere on the board
SCK: IC1.3 ((PCINT15/SCK)PB7); also elsewhere on the board
SCL: IC1.19 ((PCINT16/SCL)PC0); also elsewhere on the board
SDA: IC1.20 ((PCINT17/SDA)PC1); also elsewhere on the board
SDA_CTRL: IC1.24 ((PCINT21/TDI)PC5); also elsewhere on the board
SD_CD: IC1.41 ((PCINT9/CLKO/T1)PB1); also elsewhere on the board
SD_CS: IC1.44 ((PCINT12/OC0B/~SS)PB4); also elsewhere on the board
TX: IC1.10 ((PCINT25/TXD0)PD1); also elsewhere on the board
TX_EXT: IC1.12 ((PCINT27/INT1)PD3); also elsewhere on the board
~LED_EN: IC1.40 ((PCINT8/XCK0/T0)PB0); also elsewhere on the board

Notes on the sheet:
Pin 23
Pin A5/29
Pin 4
Pin 20
Pin 6
Pin 0
Pin 11
Pin 16
Pin 5
Reset
Pin 18
Pin 15
Pin 19
Pin A3/27
Add: GPIO1 GPIO3
Pin A6/30
Pin 1
Pin A1/25
Pin 10
Pin 22
Pin A4/28
Pin A2/26
Pin A0/24
Pin 8
Pin 12
Pin 13
Pin 2
Microcontroller
Pin 3
Pin 17
ATmega1284
Pin 14
Pin A7/31
Pin 9
Clock
Pin 7
Pin 21

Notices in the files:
README.md:
This work is licensed under a Creative Commons Attribution-ShareAlike 4.0 International License.
